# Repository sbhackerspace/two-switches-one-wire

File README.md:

# two-switches-one-wire
IRL space team controller, but different.

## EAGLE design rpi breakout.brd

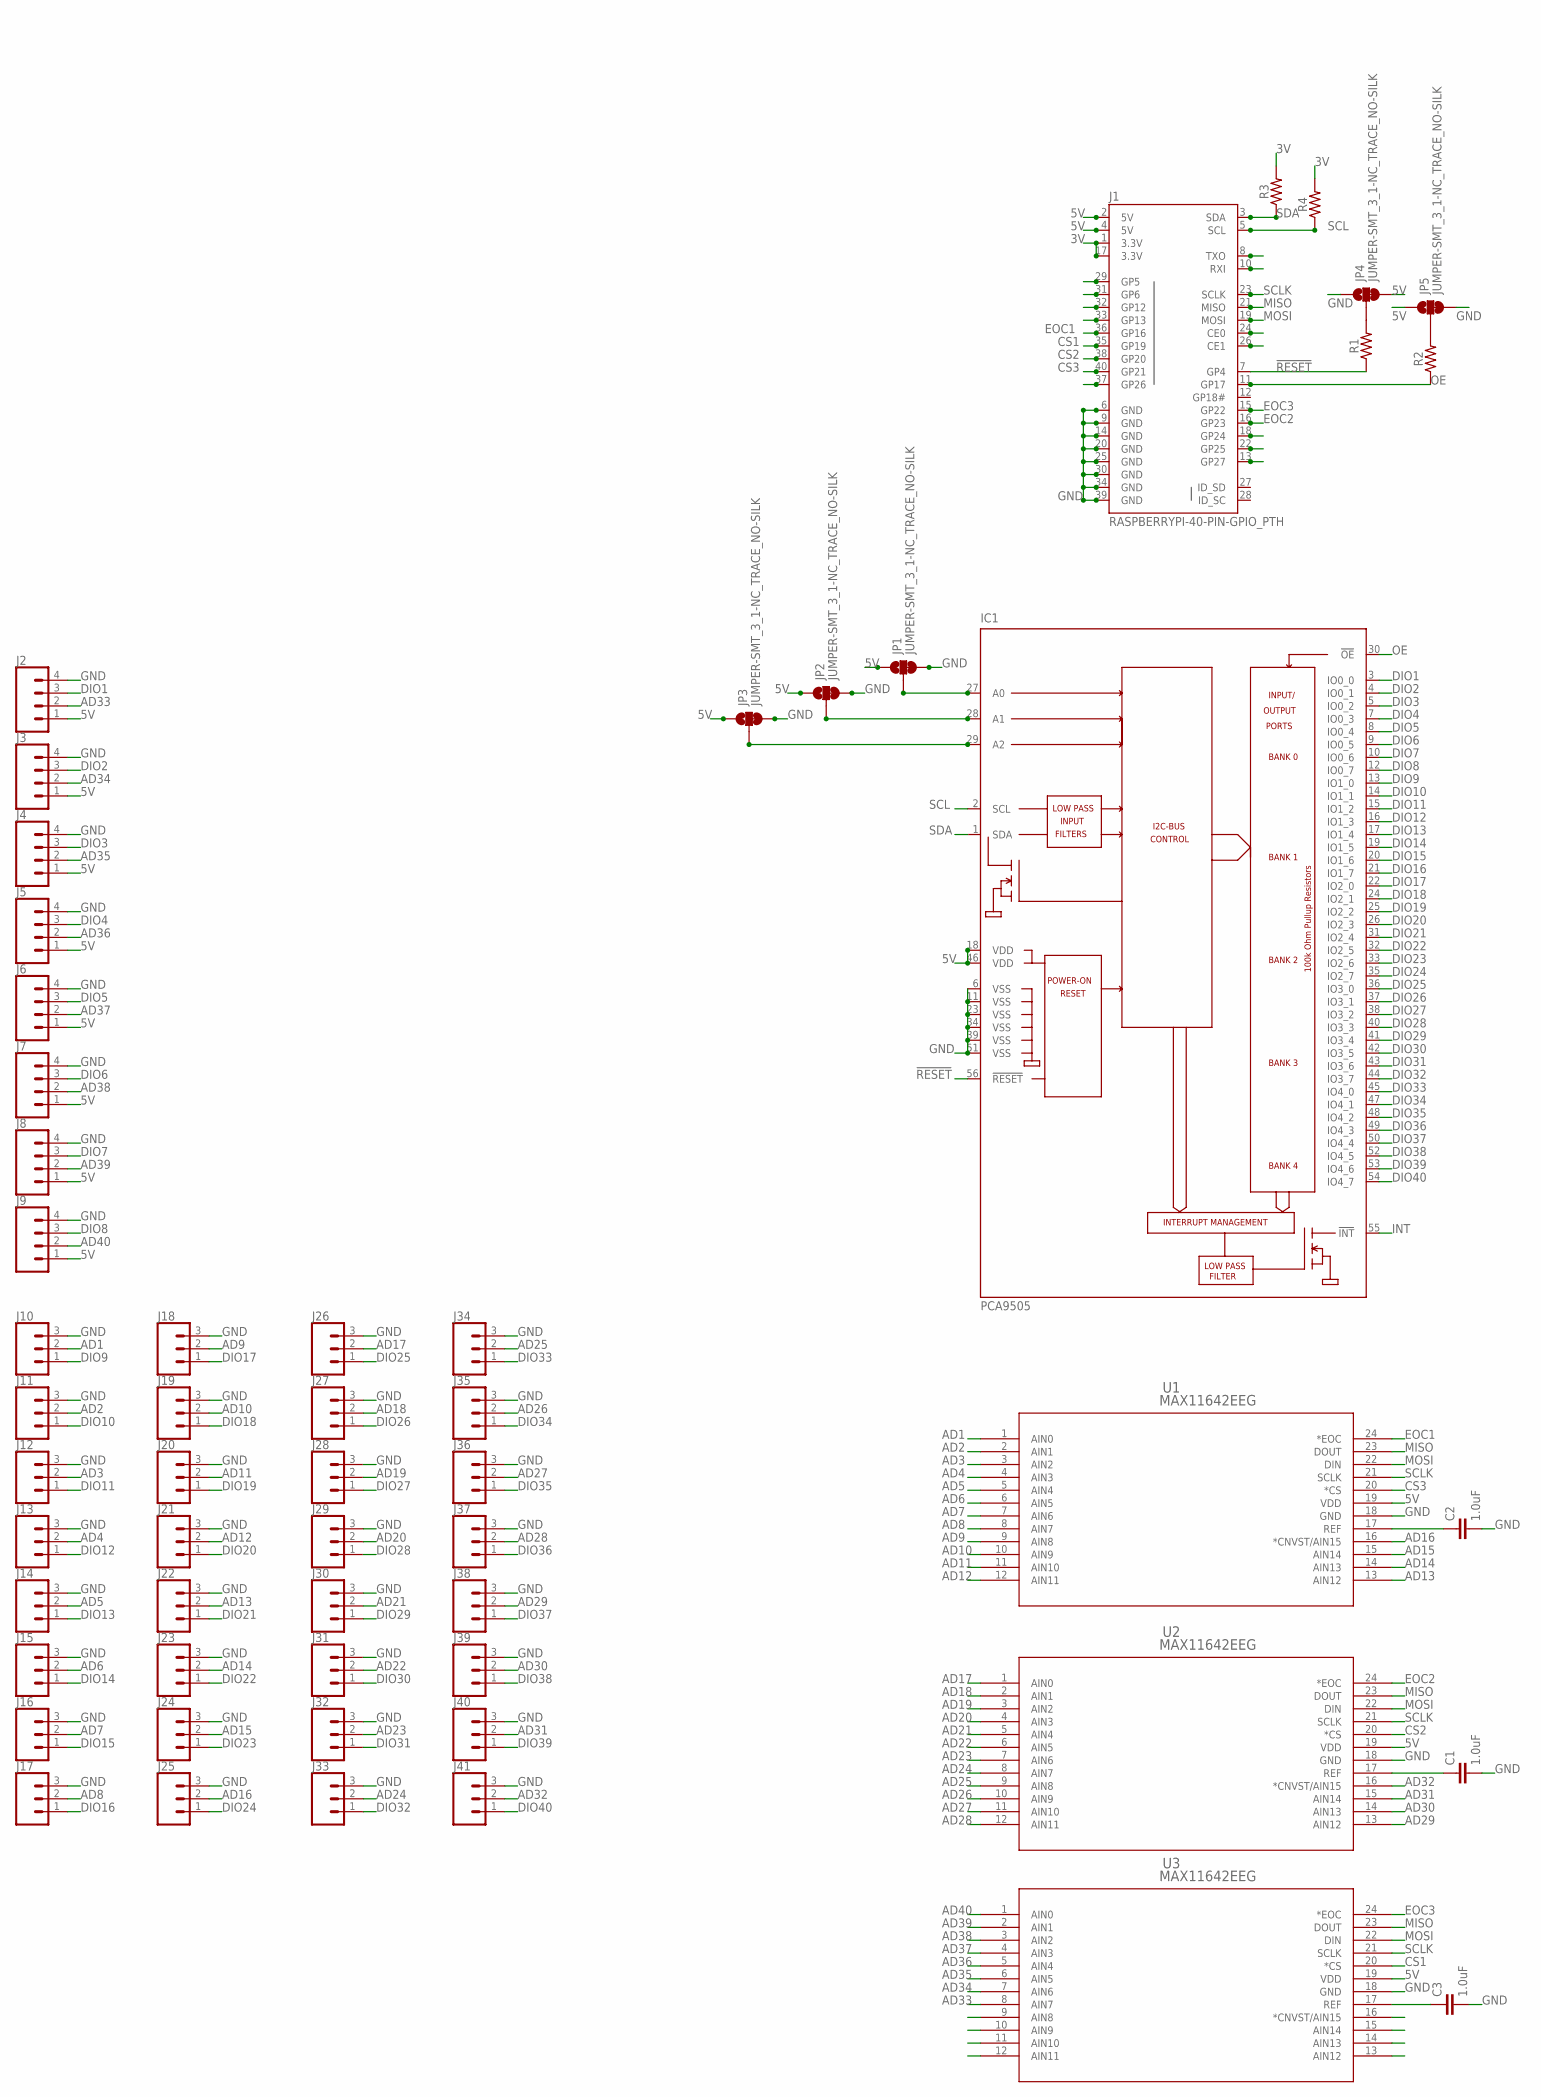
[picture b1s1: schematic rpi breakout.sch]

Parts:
C1, C2, C3: 1.0uF; 0805
IC1: PCA9505; TSSOP56-6
J1: RASPBERRYPI-40-PIN-GPIO_PTH; 2X20_SHROUDED
J2, J3, J4, J5, J6, J7, J8, J9: CONN_04JST-PTH; JST-4-PTH
J10, J11, J12, J13, J14, J15, J16, J17, J18, J19, J20, J21, J22, J23, J24, J25, J26, J27, J28, J29, J30, J31, J32, J33, J34, J35, J36, J37, J38, J39, J40, J41: CONN_03JST-PTH; JST-3-PTH
JP1, JP2, JP3, JP4, JP5: JUMPER-SMT_3_1-NC_TRACE_NO-SILK; SMT-JUMPER_3_1-NC_TRACE_NO-SILK
R1, R2, R3, R4: 0805
U1, U2, U3: MAX11642EEG; 21-0055H_24

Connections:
3V: J1.1 (3.3V), J1.17 (3.3V), R3.2, R4.2
5V: IC1.18 (VDD), IC1.46 (VDD), J1.2 (5V), J1.4 (5V), J2.1, J3.1, J4.1, J5.1, J6.1, J7.1, J8.1, J9.1, JP1.1, JP2.1, JP3.1, JP4.3, JP5.1, U1.19 (VDD), U2.19 (VDD), U3.19 (VDD)
!RESET: IC1.56 (!RESET), J1.7 (GP4), R1.1
AD1: J10.2, U1.1 (AIN0)
AD2: J11.2, U1.2 (AIN1)
AD3: J12.2, U1.3 (AIN2)
AD4: J13.2, U1.4 (AIN3)
AD5: J14.2, U1.5 (AIN4)
AD6: J15.2, U1.6 (AIN5)
AD7: J16.2, U1.7 (AIN6)
AD8: J17.2, U1.8 (AIN7)
AD9: J18.2, U1.9 (AIN8)
AD10: J19.2, U1.10 (AIN9)
AD11: J20.2, U1.11 (AIN10)
AD12: J21.2, U1.12 (AIN11)
AD13: J22.2, U1.13 (AIN12)
AD14: J23.2, U1.14 (AIN13)
AD15: J24.2, U1.15 (AIN14)
AD16: J25.2, U1.16 (*CNVST/AIN15)
AD17: J26.2, U2.1 (AIN0)
AD18: J27.2, U2.2 (AIN1)
AD19: J28.2, U2.3 (AIN2)
AD20: J29.2, U2.4 (AIN3)
AD21: J30.2, U2.5 (AIN4)
AD22: J31.2, U2.6 (AIN5)
AD23: J32.2, U2.7 (AIN6)
AD24: J33.2, U2.8 (AIN7)
AD25: J34.2, U2.9 (AIN8)
AD26: J35.2, U2.10 (AIN9)
AD27: J36.2, U2.11 (AIN10)
AD28: J37.2, U2.12 (AIN11)
AD29: J38.2, U2.13 (AIN12)
AD30: J39.2, U2.14 (AIN13)
AD31: J40.2, U2.15 (AIN14)
AD32: J41.2, U2.16 (*CNVST/AIN15)
AD33: J2.2, U3.8 (AIN7)
AD34: J3.2, U3.7 (AIN6)
AD35: J4.2, U3.6 (AIN5)
AD36: J5.2, U3.5 (AIN4)
AD37: J6.2, U3.4 (AIN3)
AD38: J7.2, U3.3 (AIN2)
AD39: J8.2, U3.2 (AIN1)
AD40: J9.2, U3.1 (AIN0)
CS1: J1.35 (GP19), U3.20 (*CS)
CS2: J1.38 (GP20), U2.20 (*CS)
CS3: J1.40 (GP21), U1.20 (*CS)
DIO1: IC1.3 (IO0_0), J2.3
DIO2: IC1.4 (IO0_1), J3.3
DIO3: IC1.5 (IO0_2), J4.3
DIO4: IC1.7 (IO0_3), J5.3
DIO5: IC1.8 (IO0_4), J6.3
DIO6: IC1.9 (IO0_5), J7.3
DIO7: IC1.10 (IO0_6), J8.3
DIO8: IC1.12 (IO0_7), J9.3
DIO9: IC1.13 (IO1_0), J10.1
DIO10: IC1.14 (IO1_1), J11.1
DIO11: IC1.15 (IO1_2), J12.1
DIO12: IC1.16 (IO1_3), J13.1
DIO13: IC1.17 (IO1_4), J14.1
DIO14: IC1.19 (IO1_5), J15.1
DIO15: IC1.20 (IO1_6), J16.1
DIO16: IC1.21 (IO1_7), J17.1
DIO17: IC1.22 (IO2_0), J18.1
DIO18: IC1.24 (IO2_1), J19.1
DIO19: IC1.25 (IO2_2), J20.1
DIO20: IC1.26 (IO2_3), J21.1
DIO21: IC1.31 (IO2_4), J22.1
DIO22: IC1.32 (IO2_5), J23.1
DIO23: IC1.33 (IO2_6), J24.1
DIO24: IC1.35 (IO2_7), J25.1
DIO25: IC1.36 (IO3_0), J26.1
DIO26: IC1.37 (IO3_1), J27.1
DIO27: IC1.38 (IO3_2), J28.1
DIO28: IC1.40 (IO3_3), J29.1
DIO29: IC1.41 (IO3_4), J30.1
DIO30: IC1.42 (IO3_5), J31.1
DIO31: IC1.43 (IO3_6), J32.1
DIO32: IC1.44 (IO3_7), J33.1
DIO33: IC1.45 (IO4_0), J34.1
DIO34: IC1.47 (IO4_1), J35.1
DIO35: IC1.48 (IO4_2), J36.1
DIO36: IC1.49 (IO4_3), J37.1
DIO37: IC1.50 (IO4_4), J38.1
DIO38: IC1.52 (IO4_5), J39.1
DIO39: IC1.53 (IO4_6), J40.1
DIO40: IC1.54 (IO4_7), J41.1
EOC1: J1.36 (GP16), U1.24 (*EOC)
EOC2: J1.16 (GP23), U2.24 (*EOC)
EOC3: J1.15 (GP22), U3.24 (*EOC)
GND: C1.2, C2.2, C3.2, IC1.6 (VSS), IC1.11 (VSS), IC1.23 (VSS), IC1.34 (VSS), IC1.39 (VSS), IC1.51 (VSS), J1.6 (GND), J1.9 (GND), J1.14 (GND), J1.20 (GND), J1.25 (GND), J1.30 (GND), J1.34 (GND), J1.39 (GND), J2.4, J3.4, J4.4, J5.4, J6.4, J7.4, J8.4, J9.4, J10.3, J11.3, J12.3, J13.3, J14.3, J15.3, J16.3, J17.3, J18.3, J19.3, J20.3, J21.3, J22.3, J23.3, J24.3, J25.3, J26.3, J27.3, J28.3, J29.3, J30.3, J31.3, J32.3, J33.3, J34.3, J35.3, J36.3, J37.3, J38.3, J39.3, J40.3, J41.3, JP1.3, JP2.3, JP3.3, JP4.1, JP5.3, U1.18 (GND), U2.18 (GND), U3.18 (GND)
INT: IC1.55 (!INT)
MISO: J1.21 (MISO), U1.23 (DOUT), U2.23 (DOUT), U3.23 (DOUT)
MOSI: J1.19 (MOSI), U1.22 (DIN), U2.22 (DIN), U3.22 (DIN)
unnamed: JP4.2, R1.2
unnamed: C3.1, U3.17 (REF)
unnamed: C1.1, U2.17 (REF)
unnamed: JP5.2, R2.2
unnamed: C2.1, U1.17 (REF)
unnamed: IC1.27 (A0), JP1.2
unnamed: IC1.28 (A1), JP2.2
unnamed: IC1.29 (A2), JP3.2
OE: IC1.30 (!OE), J1.11 (GP17), R2.1
SCL: IC1.2 (SCL), J1.5 (SCL), R4.1
SCLK: J1.23 (SCLK), U1.21 (SCLK), U2.21 (SCLK), U3.21 (SCLK)
SDA: IC1.1 (SDA), J1.3 (SDA), R3.1
SDA1: J1.13 (GP27)

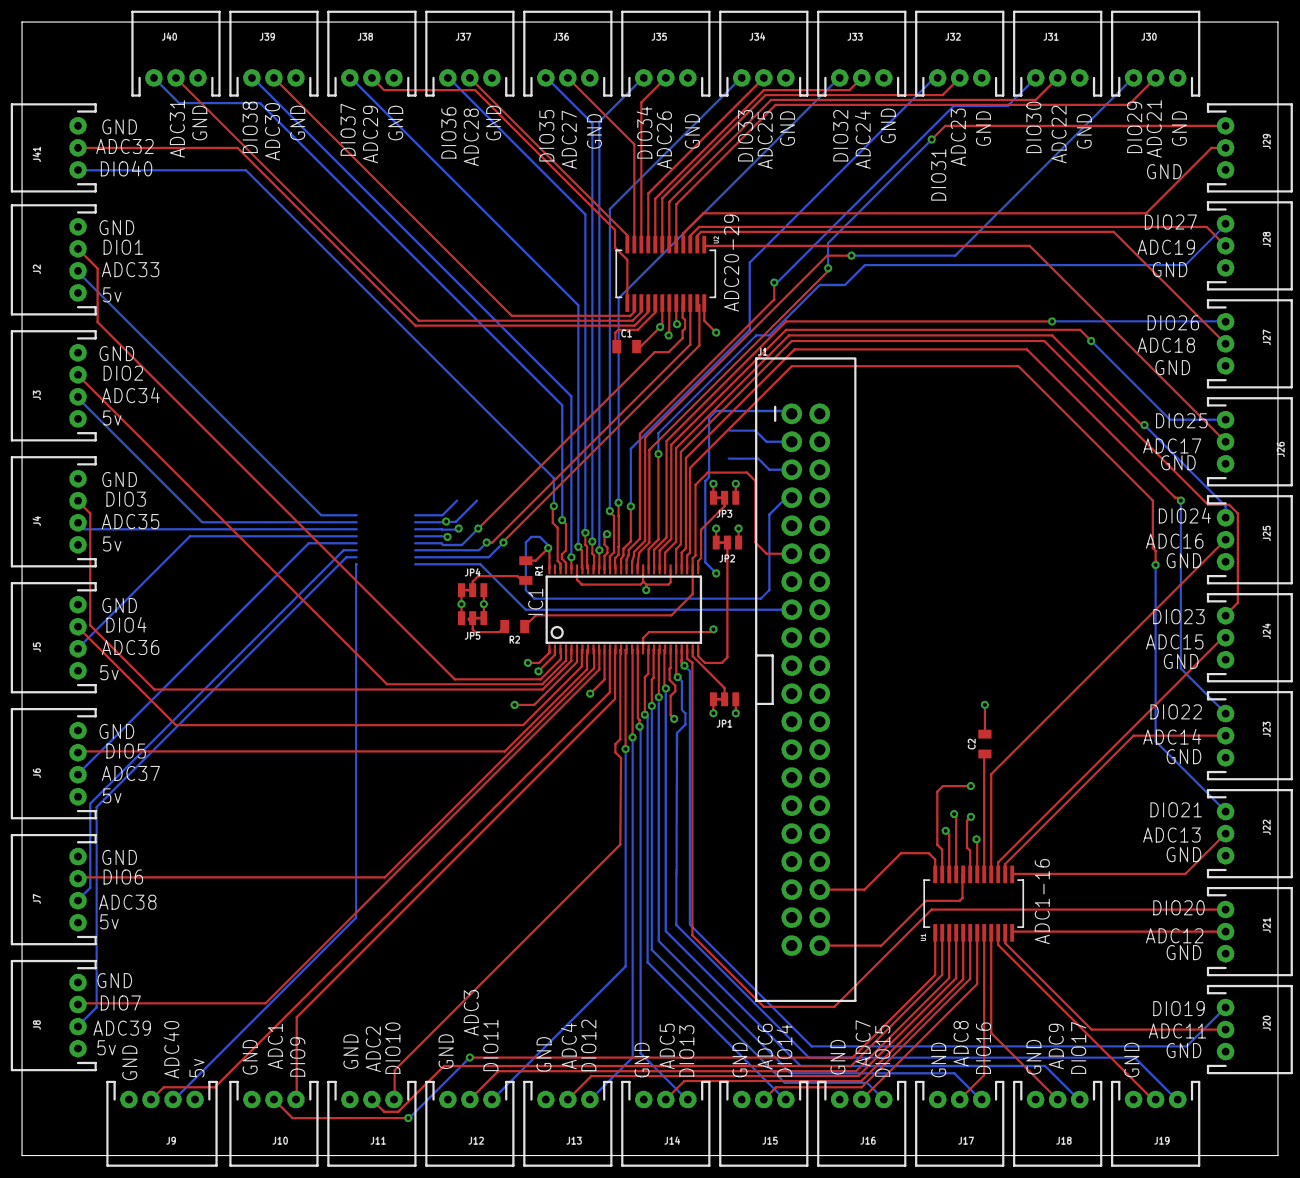
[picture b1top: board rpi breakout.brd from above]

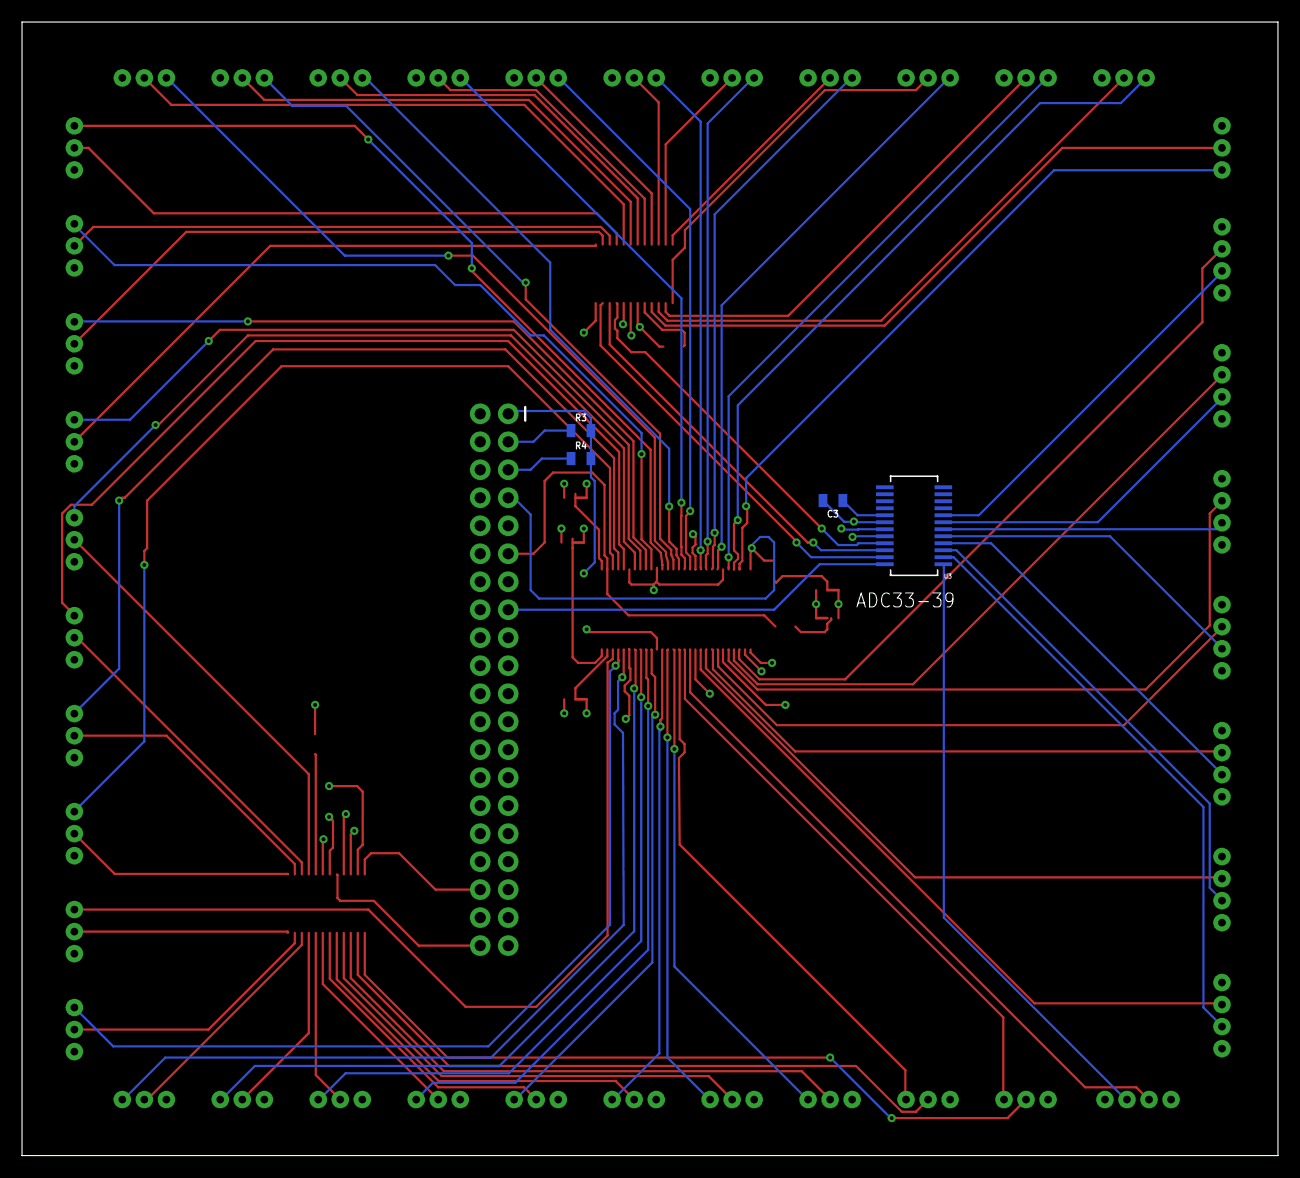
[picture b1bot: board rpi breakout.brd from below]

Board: 4 copper layers, 114.0 x 102.9 mm, 57 parts (4 on the bottom side), 104 nets.

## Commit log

2019-03-13 IO expander board initial upload
2019-03-16 PCB pass two
    all routing completed except arefs
2019-03-18 added video
2019-03-22 FInal routing pass
    connected remaining pins, added decoupling caps to AREF pins.
2019-03-28 pulled OE and Reset lines to 5v and ground
2019-03-28 added i2c pull ups
2019-03-31 updated silkscreen and increased trace sizes
    increased sizes of all traces and update routing to clear DRC. Added silkscreen for all connections. Sent to fab
2019-04-12 Added Setup json
    added items to setup.json
2019-04-12 added momentary
    added a momentary button
2019-04-12 added tribute buttons
    buttons for mike, billy, dan, eric(s), and mark who put a lot of work into this project
2019-04-12 added more analog inputs
    what the title says
2019-04-12 fixed analog thresholds
    fixed an error in analog thresholds with overlapping values. Added more stuff
2019-04-12 more analog inputs
    added more analog inputs
2019-04-12 added more
    more stuff
2019-05-26 fixed silkscreen numbering
    fixed adc silkscreen numbering
2019-08-14 added more entries
    added several of each type of input
2019-08-14 Unfucked the brackets and formatting
2019-08-14 removed duplicate inputs
2019-08-15 Added a version of setup.json with proper json structure
2019-08-15 Added some analog inputs

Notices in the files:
parts and their libraries:
SparkFun-Connectors: Licensing: Creative Commons ShareAlike 4.0 International - https://creativecommons.org/licenses/by-sa/4.0
